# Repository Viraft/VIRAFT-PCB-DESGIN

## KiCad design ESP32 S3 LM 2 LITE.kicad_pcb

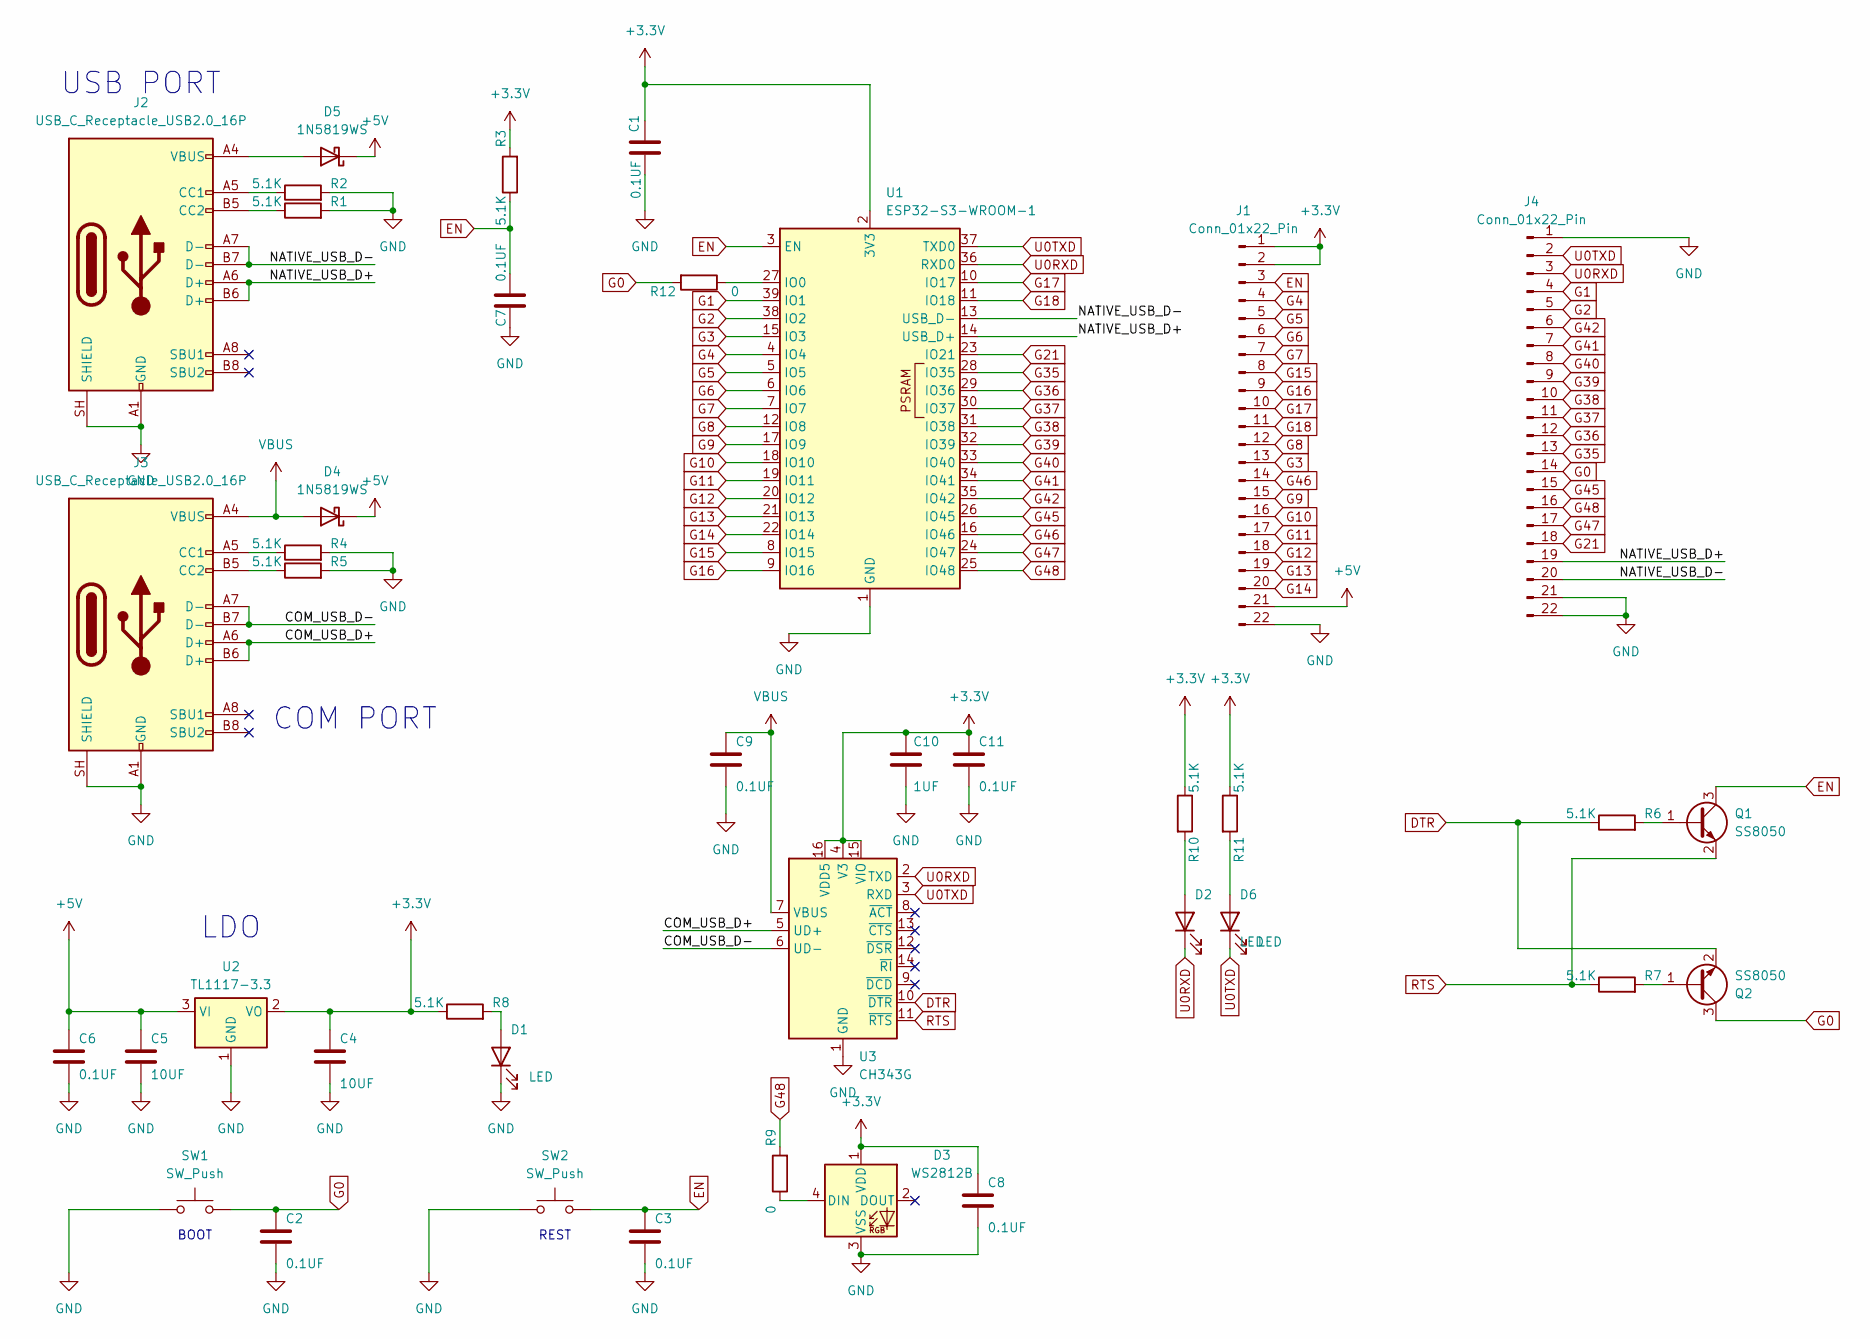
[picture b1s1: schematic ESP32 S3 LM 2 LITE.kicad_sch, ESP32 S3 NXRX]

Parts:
C1, C2, C3, C6, C7, C8, C9, C11: 0.1UF; C_0603_1608Metric
C4, C5: 10UF; C_0805_2012Metric
C10: 1UF; C_0603_1608Metric
D1, D2, D6: LED; LED_0603_1608Metric_Pad1.05x0.95mm_HandSolder
D3: WS2812B; LED_WS2812B_PLCC4_5.0x5.0mm_P3.2mm
D4, D5: 1N5819WS; D_SOD-323
J1, J4: Conn_01x22_Pin; PinHeader_1x22_P2.54mm_Vertical
J2, J3: USB_C_Receptacle_USB2.0_16P; USB_C_Receptacle_GCT_USB4105-xx-A_16P_TopMnt_Horizontal
Q1, Q2: SS8050; SOT-23
R1, R2, R3, R4, R5, R6, R7, R8, R10, R11: 5.1K; R_0603_1608Metric
R9, R12: 0; R_0603_1608Metric
SW1, SW2: SW_Push; SW_SPST_PTS810
U1: ESP32-S3-WROOM-1
U2: TL1117-3.3; SOT-223-3_TabPin2
U3: CH343G; SOIC-16_3.9x9.9mm_P1.27mm

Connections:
+3.3V: C1.1, C4.1, C8.1, C10.2, C11.2, D3.1 (VDD), J1.1, J1.2, R3.2, R8.1, R10.1, R11.1, U1.2 (3V3), U2.2 (VO), U3.4 (V3), U3.15 (VIO), U3.16 (VDD5)
+5V: C5.1, C6.1, D4.1 (K), D5.1 (K), J1.21, U2.3 (VI)
/COM_USB_D+: J3.A6 (D+), J3.B6 (D+), U3.5 (UD+)
/COM_USB_D-: J3.A7 (D-), J3.B7 (D-), U3.6 (UD-)
/NATIVE_USB_D+: J2.A6 (D+), J2.B6 (D+), J4.19, U1.14 (USB_D+)
/NATIVE_USB_D-: J2.A7 (D-), J2.B7 (D-), J4.20, U1.13 (USB_D-)
DTR: Q2.2 (E), R6.1, U3.10 (~DTR)
EN: C3.1, C7.1, J1.3, Q1.3 (C), R3.1, SW2.2, U1.3 (EN)
G0: C2.1, J4.14, Q2.3 (C), R12.2, SW1.2
G1: J4.4, U1.39 (IO1)
G2: J4.5, U1.38 (IO2)
G3: J1.13, U1.15 (IO3)
G4: J1.4, U1.4 (IO4)
G5: J1.5, U1.5 (IO5)
G6: J1.6, U1.6 (IO6)
G7: J1.7, U1.7 (IO7)
G8: J1.12, U1.12 (IO8)
G9: J1.15, U1.17 (IO9)
G10: J1.16, U1.18 (IO10)
G11: J1.17, U1.19 (IO11)
G12: J1.18, U1.20 (IO12)
G13: J1.19, U1.21 (IO13)
G14: J1.20, U1.22 (IO14)
G15: J1.8, U1.8 (IO15)
G16: J1.9, U1.9 (IO16)
G17: J1.10, U1.10 (IO17)
G18: J1.11, U1.11 (IO18)
G21: J4.18, U1.23 (IO21)
G35: J4.13, U1.28 (IO35)
G36: J4.12, U1.29 (IO36)
G37: J4.11, U1.30 (IO37)
G38: J4.10, U1.31 (IO38)
G39: J4.9, U1.32 (IO39)
G40: J4.8, U1.33 (IO40)
G41: J4.7, U1.34 (IO41)
G42: J4.6, U1.35 (IO42)
G45: J4.15, U1.26 (IO45)
G46: J1.14, U1.16 (IO46)
G47: J4.17, U1.24 (IO47)
G48: J4.16, R9.2, U1.25 (IO48); also elsewhere on the board
GND: C1.2, C2.2, C3.2, C4.2, C5.2, C6.2, C7.2, C8.2, C9.1, C10.1, C11.1, D1.1 (K), D3.3 (VSS), J1.22, J2.A1 (GND), J2.A12 (GND), J2.B1 (GND), J2.B12 (GND), J2.SH (SHIELD), J3.A1 (GND), J3.A12 (GND), J3.B1 (GND), J3.B12 (GND), J3.SH (SHIELD), J4.1, J4.21, J4.22, R1.2, R2.2, R4.2, R5.2, SW1.1, SW2.1, U1.1 (GND), U1.40 (GND), U1.41 (GND), U2.1 (GND), U3.1 (GND)
unnamed: D1.2 (A), R8.2
unnamed: D2.2 (A), R10.2
unnamed 43: D3.4 (DIN), R9.1; also elsewhere on the board
unnamed: D5.2 (A), J2.A4 (VBUS), J2.A9 (VBUS), J2.B4 (VBUS), J2.B9 (VBUS)
unnamed: D6.2 (A), R11.2
unnamed: J2.A5 (CC1), R2.1
unnamed: J2.B5 (CC2), R1.1
unnamed: J3.A5 (CC1), R4.1
unnamed: J3.B5 (CC2), R5.1
unnamed: Q1.1 (B), R6.2
unnamed: Q2.1 (B), R7.2
unnamed: R12.1, U1.27 (IO0)
RTS: Q1.2 (E), R7.1, U3.11 (~RTS)
U0RXD: D2.1 (K), J4.3, U1.36 (RXD0), U3.2 (TXD)
U0TXD: D6.1 (K), J4.2, U1.37 (TXD0), U3.3 (RXD)
VBUS: C9.2, D4.2 (A), J3.A4 (VBUS), J3.A9 (VBUS), J3.B4 (VBUS), J3.B9 (VBUS), U3.7 (VBUS)

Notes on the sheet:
LDO
REST
COM PORT
BOOT
USB PORT

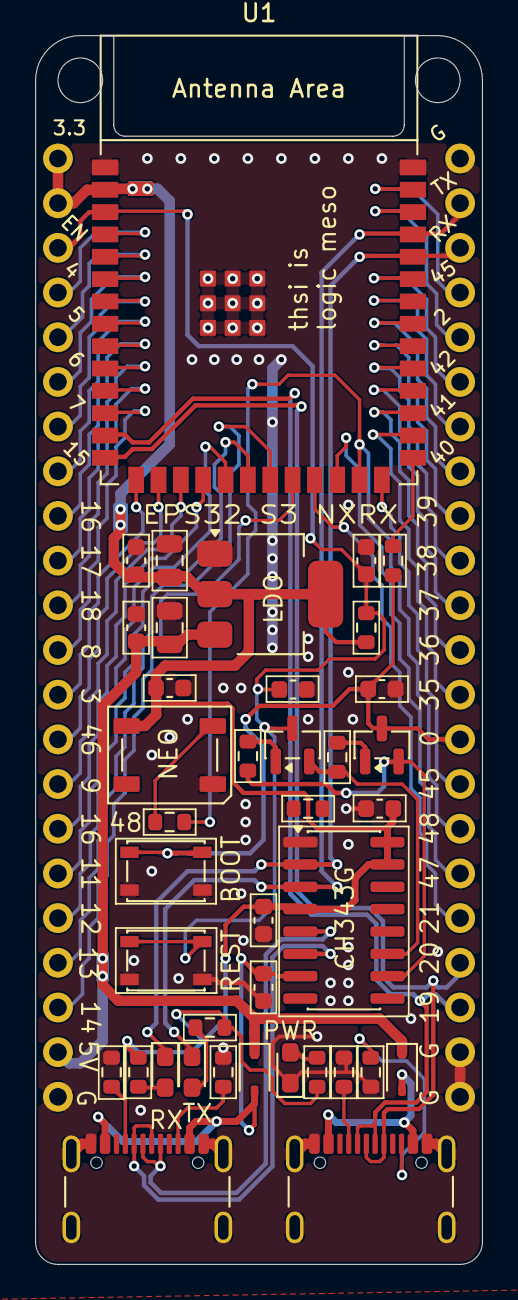
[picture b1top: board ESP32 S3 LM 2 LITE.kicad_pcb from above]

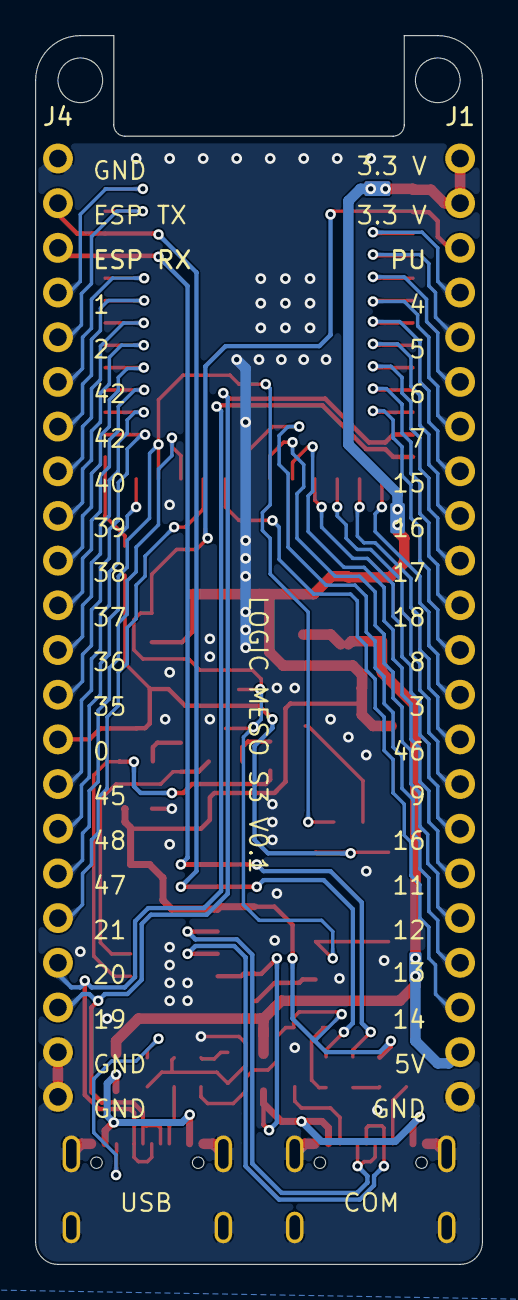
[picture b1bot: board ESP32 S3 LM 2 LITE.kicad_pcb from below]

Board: 2 copper layers, 25.4 x 69.8 mm, 41 parts (2 on the bottom side), 57 nets.

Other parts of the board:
R9#2: 0; R_0603_1608Metric

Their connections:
G48: R9#2.2; also elsewhere on the board
unnamed 43: R9#2.1; also elsewhere on the board

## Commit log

2026-06-20 Add files via upload
    A UPDATED VERIOSN FINISHED NOT REVIEW BY OTHER YET
